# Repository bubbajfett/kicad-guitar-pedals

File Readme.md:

# Current guitar pedal projects 

Current count of pedals in this repo is:  36(?).    Not doing too many more, though I have a FV-1 and a Daisy seed one I'm working on longer term, as well as clearing out the box of shame.

The requirements here are KICAD 7 or later.     Each subdir has a gerbers directory, which has the final set of gerbers used.    

The latest change is to add a PDF in the root of each pedal directory, which has the readme, the schematic as an image, and the front and back layout of the PCB (F.Cu+F.Silkscreen, B.Cu+F.Silkscreen). Also a BOM of the parts is included.    This was all done scripted using kicad-cli  in a VM (Fedora 44, Kicad 10 !!!) as the Kicad 7 versions of this did not work very well.   I will add pics of the real tested boards as an addendum to these.    This change was a result of some feedback I recieved about the lack of clarity of what is in this repo.

These pedals have been a learning exercise for me in KiCad. Any guitar pedal PCB published here has been built and tested. In some cases, more than two versions of boards have been created.   The worst case was 5 versions.

The main idea for doing my own PCB is to allow me to change the footprints and merge and/or hack pedal schematics to come up with new ideas.
The other reason is I am redoing my pedalboard to convert from side-jacks/veroboard layout to  top-jacks/pcbs.   I have gotten to dislike veroboard layouts.

I am an amateur in this.   Also this has been a huge learning exercise.    I've tried to be consistent with some design decisions.

*   back of board mounted POTs.   Tried using both 16mm and 9mm pots (RK97?)
*   common format pinheader so to be able to use 4pin dupont connector or JST connector when building.   The topjacks pcb broke this "common format (9v, Out, In, Gnd --- from left to right)",
in that it was initially intended that the PCB be oriented closest to the the 125B shell bottom, but that made assembly more difficult.   I ordered panels of it from JLPCB, and so I;m just wiring them
backwards.
*   power on the top jack connector, with diode protection there.
*   led on the stomp switch
*   125B form factor.    Top jacks in a 1590B is really hard unless the power connector is modified or moved somewhere else.

One thing I have learned is that the text size on some of these boards is below
the JLPCB minimum recommended size; the text looks fine in osh-park boards.

Several of the build docs have pictures of the final builds.    Tonemachine is the latest...

Putting these pedal layouts out there for any interested party.   Do what you want with them. 

Here are the current repo contents.   These have all been tested outside the box,
and multiple have been successfully boxed.  12  have been boxed and are 
now on the pedalboard. 

| PEDAL | BUILD DOC | Verified|
| ----  | -------   | ------- |
| Delay/deep_blue_delay | [deep-blue-delay](./Delay/deep_blue_delay/deep_blue_delay.pdf) | Y |
| Util/stomp-chargepump |  [stomp-chargepump](./Util/stomp-chargepump/stomp-chargepump.pdf) | Y |
| Util/stomp-3pdt | [stomp-3pdt](./Util/stomp-3pdt/stomp-3pdt.pdf) | Y | 
| Util/top-jacks | [top-jacks](./Util/top-jacks/top-jacks.pdf) | Y |
| Distortion/percolator | [percolator](./Distortion/percolator/percolator.pdf) | Y |
| Distortion/acapulcogold | [acapulcogold](./Distortion/acapulcogold/acapulcogold.pdf) | Y |
| Distortion/fuzzface | [fuzzface](./Distortion/fuzzface/fuzzface.pdf) | Y | 
| Distortion/redllama | [redllama](./Distortion/redllama/redllama.pdf) | Y |
| Distortion/whitefuzz | [whitefuzz](./Distortion/whitefuzz/whitefuzz.pdf) | Y |
| Distortion/bigmuff | [bigmuff](./Distortion/bigmuff/bigmuff.pdf) | Y | 
| Distortion/bigmuff/bmp-ramshead  | --- | Y |
| Distortion/lizardq | [lizardq](./Distortion/lizardq/lizardq.pdf) | Y | 
| Distortion/ejfuzzface | [ejfuzzface](./Distortion/ejfuzzface/ejfuzzface.pdf) | Y | 
| Distortion/tonemachine | [tonemachine](./Distortion/tonemachine/tonemachine.pdf) | Y |
| Distortion/bmp2 | --- | Y |
| Distortion/blackdarling | --- | Y |
| Distortion/900fuzz | --- | Y |
| Compressor/bearhug | [bearhug](./Compressor/bearhug/bearhug.pdf) | Y | 
| Compressor/engineers_thumb | [engineers_thumb](./Compressor/engineers_thumb/engineers_thumb.pdf) | Y |
| Compressor/dynacomp | --- | Y |
| Compressor/dynacomp-lm13700  | --- | N |
| Chorus/littleangel | [littleangel](./Chorus/littleangel/littleangel.pdf) | Y |
| Envelope/mutron | [mutron-v](./Envelope/mutron/mutron.pdf) | Y |
| Overdrive/SFTii | [sftii](./Overdrive/SFTii/SFTii.pdf) | Y | 
| Overdrive/triple_wreck | [triple_wreck](./Overdrive/triple_wreck/triple_wreck.pdf) | Y | 
| Overdrive/ecstacy | [ecstacy](./Overdrive/ecstacy/ecstacy.pdf) | Y | 
| Overdrive/badmonkey | [badmonkey](./Overdrive/badmonkey/badmonkey.pdf) | Y |
| Overdrive/bsiab |  [bsiab](./Overdrive/bsiab/bsiab.pdf) | Y |
| Overdrive/fatdrive | [fatdrive](./Overdrive/fatdrive/fatdrive.pdf)| Y |
| Overdrive/tweed57 | [tweed57](./Overdrive/tweed57/tweed57.pdf)|Y|
| Overdrive/timmy  | [timmy](./Overdrive/timmy/timmy.pdf) | Y |
| Overdrive/KoT | [KoT](./Overdrive/KoT/KoT.pdf) | Y | 
| Overdrive/ocd | [ocd](./Overdrive/ocd/ocd.pdf) | Y |
| Overdrive/revv-g4 | [revv-g4](./Overdrive/revv-g4/revv-g4.pdf) | Y |
| Overdrive/drboogie | ... | Y |
| Overdrive/umble | [umble](./Overdrive/umble/umble.pdf) | Y |
| Equalizer/eq | [eq](./Equalizer/eq/eq.pdf) | Y | 

PCB builds in progress are

*   Barbershop (redo)
*   Klon
*   phase45
*   g2
*   beod    (built, passes sound, but *** so much noise).
*   fy2  (shin-ey fy2)
*   bluesdriver
*   brutalist Jr
*   fortinfuzz
*   katzenkonig
*   paisley
*   plexidrive
*   sabbracadabra
*   tubescreamer

And 4 are stuck in the box of shame 
*   zombiechorus (9 months non-working...)
*   causalty4 phaser  (ugggh ... so close)
*   box of metal      
*   kraken

All the above subprojects have a gerbers/ subdir with the last gerber file I generated. Using OshPark for pcb generation.    They were done with Kicad 7.
Most were done with manual placement of the elements on the PCB, and then using freerouting to autoroute the traces.

License is the general Creative Commons.     Have fun!

All registered trademarks are owned by their respective owners.

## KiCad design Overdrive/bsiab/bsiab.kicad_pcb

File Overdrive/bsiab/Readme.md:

# bsiab

Brown sound in a box.   

Tagboardeffects site introduces it as:

> Brown Sound In A Box version
> 2 (BSIAB2) is an excellent distortion pedal designed by Ed
> Guidry. Based on the AMZ MiniBooster cascading work done by Jack Orman
> and further refined by Aron Nelson and Doug Hammond.

> This is one of the best heavy Marshall-type distortion boxes that
> we've heard and it also performs very well on low drive setting

The schematic here is based on the General Guitar Gadgets BSIAB2 pedal

Very nice sound.

So this pedal circuit  is verified. And I have boxed this one as well.

All trademarks belong to their respective owners.

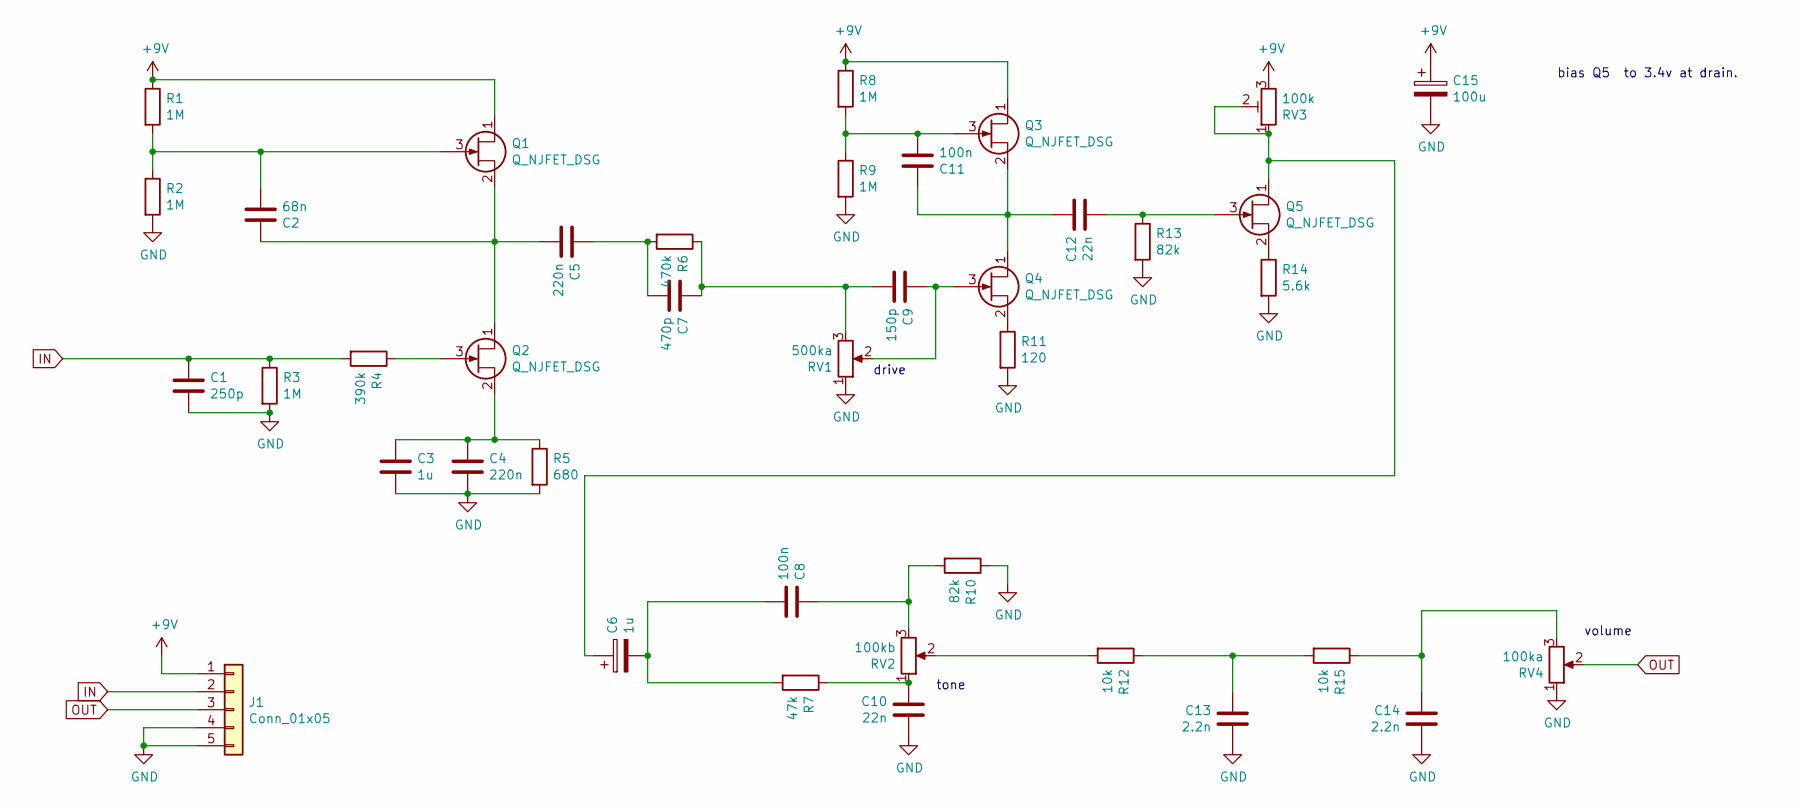
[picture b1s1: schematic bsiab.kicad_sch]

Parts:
C1: 250p; C_Disc_D5.1mm_W3.2mm_P5.00mm
C2: 68n; C_Rect_L7.0mm_W3.5mm_P2.50mm_P5.00mm
C3: 1u; C_Rect_L7.0mm_W3.5mm_P2.50mm_P5.00mm
C4, C5: 220n; C_Rect_L7.0mm_W3.5mm_P2.50mm_P5.00mm
C6: 1u; CP_Radial_D6.3mm_P2.50mm
C7: 470p; C_Disc_D5.1mm_W3.2mm_P5.00mm
C8, C11: 100n; C_Rect_L7.0mm_W3.5mm_P2.50mm_P5.00mm
C9: 150p; C_Disc_D5.1mm_W3.2mm_P5.00mm
C10, C12: 22n; C_Rect_L7.0mm_W3.5mm_P2.50mm_P5.00mm
C13, C14: 2.2n; C_Rect_L7.0mm_W3.5mm_P2.50mm_P5.00mm
C15: 100u; CP_Radial_D6.3mm_P2.50mm
J1: Conn_01x05; PinHeader_1x05_P2.54mm_Vertical
Q1, Q2, Q3, Q4, Q5: Q_NJFET_DSG; TO-92
R1, R2, R3, R8, R9: 1M; R_Axial_DIN0207_L6.3mm_D2.5mm_P10.16mm_Horizontal
R4: 390k; R_Axial_DIN0207_L6.3mm_D2.5mm_P10.16mm_Horizontal
R5: 680; R_Axial_DIN0207_L6.3mm_D2.5mm_P10.16mm_Horizontal
R6: 470k; R_Axial_DIN0207_L6.3mm_D2.5mm_P10.16mm_Horizontal
R7: 47k; R_Axial_DIN0207_L6.3mm_D2.5mm_P10.16mm_Horizontal
R10, R13: 82k; R_Axial_DIN0207_L6.3mm_D2.5mm_P10.16mm_Horizontal
R11: 120; R_Axial_DIN0207_L6.3mm_D2.5mm_P10.16mm_Horizontal
R12, R15: 10k; R_Axial_DIN0207_L6.3mm_D2.5mm_P10.16mm_Horizontal
R14: 5.6k; R_Axial_DIN0207_L6.3mm_D2.5mm_P10.16mm_Horizontal
RV1: 500ka; Potentiometer_Omeg_PC16BU_Vertical
RV2: 100kb; Potentiometer_Omeg_PC16BU_Vertical
RV3: 100k; Potentiometer_Runtron_RM-065_Vertical
RV4: 100ka; Potentiometer_Omeg_PC16BU_Vertical

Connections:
+9V: C15.1, J1.1, Q1.1 (D), Q3.1 (D), R1.1, R8.1, RV3.3
GND: C1.2, C3.2, C4.2, C10.2, C13.2, C14.2, C15.2, J1.4, J1.5, R2.2, R3.2, R5.2, R9.2, R10.1, R11.2, R13.2, R14.2, RV1.1, RV4.1
IN: C1.1, J1.2, R3.1, R4.2
unnamed: C2.1, C5.2, Q1.2 (S), Q2.1 (D)
unnamed: C2.2, Q1.3 (G), R1.2, R2.1
unnamed: C3.1, C4.1, Q2.2 (S), R5.1
unnamed: C5.1, C7.2, R6.2
unnamed: C6.1, Q5.1 (D), RV3.1, RV3.2
unnamed: C6.2, C8.2, R7.2
unnamed: C7.1, C9.2, R6.1, RV1.3
unnamed: C8.1, R10.2, RV2.3
unnamed: C9.1, Q4.3 (G), RV1.2
unnamed: C10.1, R7.1, RV2.1
unnamed: C11.1, C12.1, Q3.2 (S), Q4.1 (D)
unnamed: C11.2, Q3.3 (G), R8.2, R9.1
unnamed: C12.2, Q5.3 (G), R13.1
unnamed: C13.1, R12.1, R15.2
unnamed: C14.1, R15.1, RV4.3
unnamed: Q2.3 (G), R4.1
unnamed: Q4.2 (S), R11.1
unnamed: Q5.2 (S), R14.1
unnamed: R12.2, RV2.2
OUT: J1.3, RV4.2

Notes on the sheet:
bias Q5 to 3.4v at drain.
volume
drive
tone

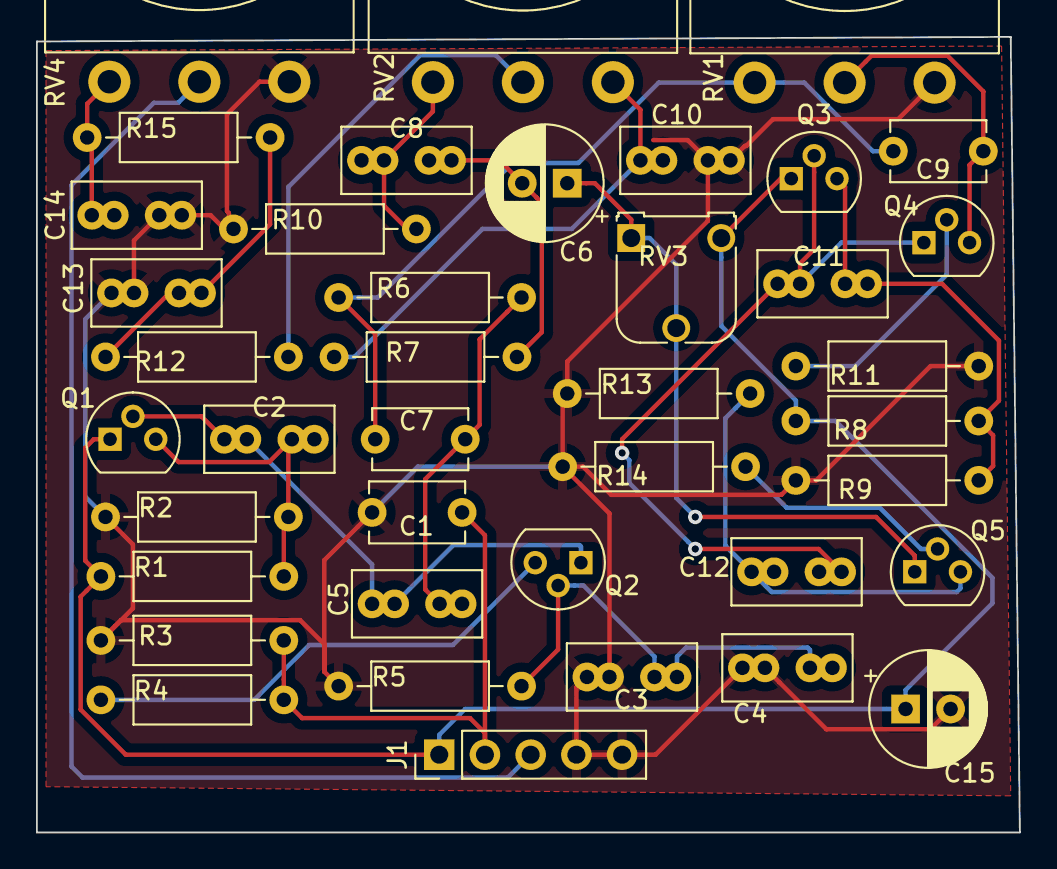
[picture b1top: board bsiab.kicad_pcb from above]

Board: 2 copper layers, 54.6 x 44.2 mm, 40 parts (0 on the bottom side), 23 nets.

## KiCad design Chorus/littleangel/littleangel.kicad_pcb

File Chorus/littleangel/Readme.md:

# Little Angel 

This is a clone Rick Holt's  Little Angel Chorus.

This was based on the a schematic I found on the web for this.
THis has the "Vibe Switch Mod" someone did,  which changes
between vibrato and chorus modes.    Nice pedal.

All trademarks belong to their respective owners.

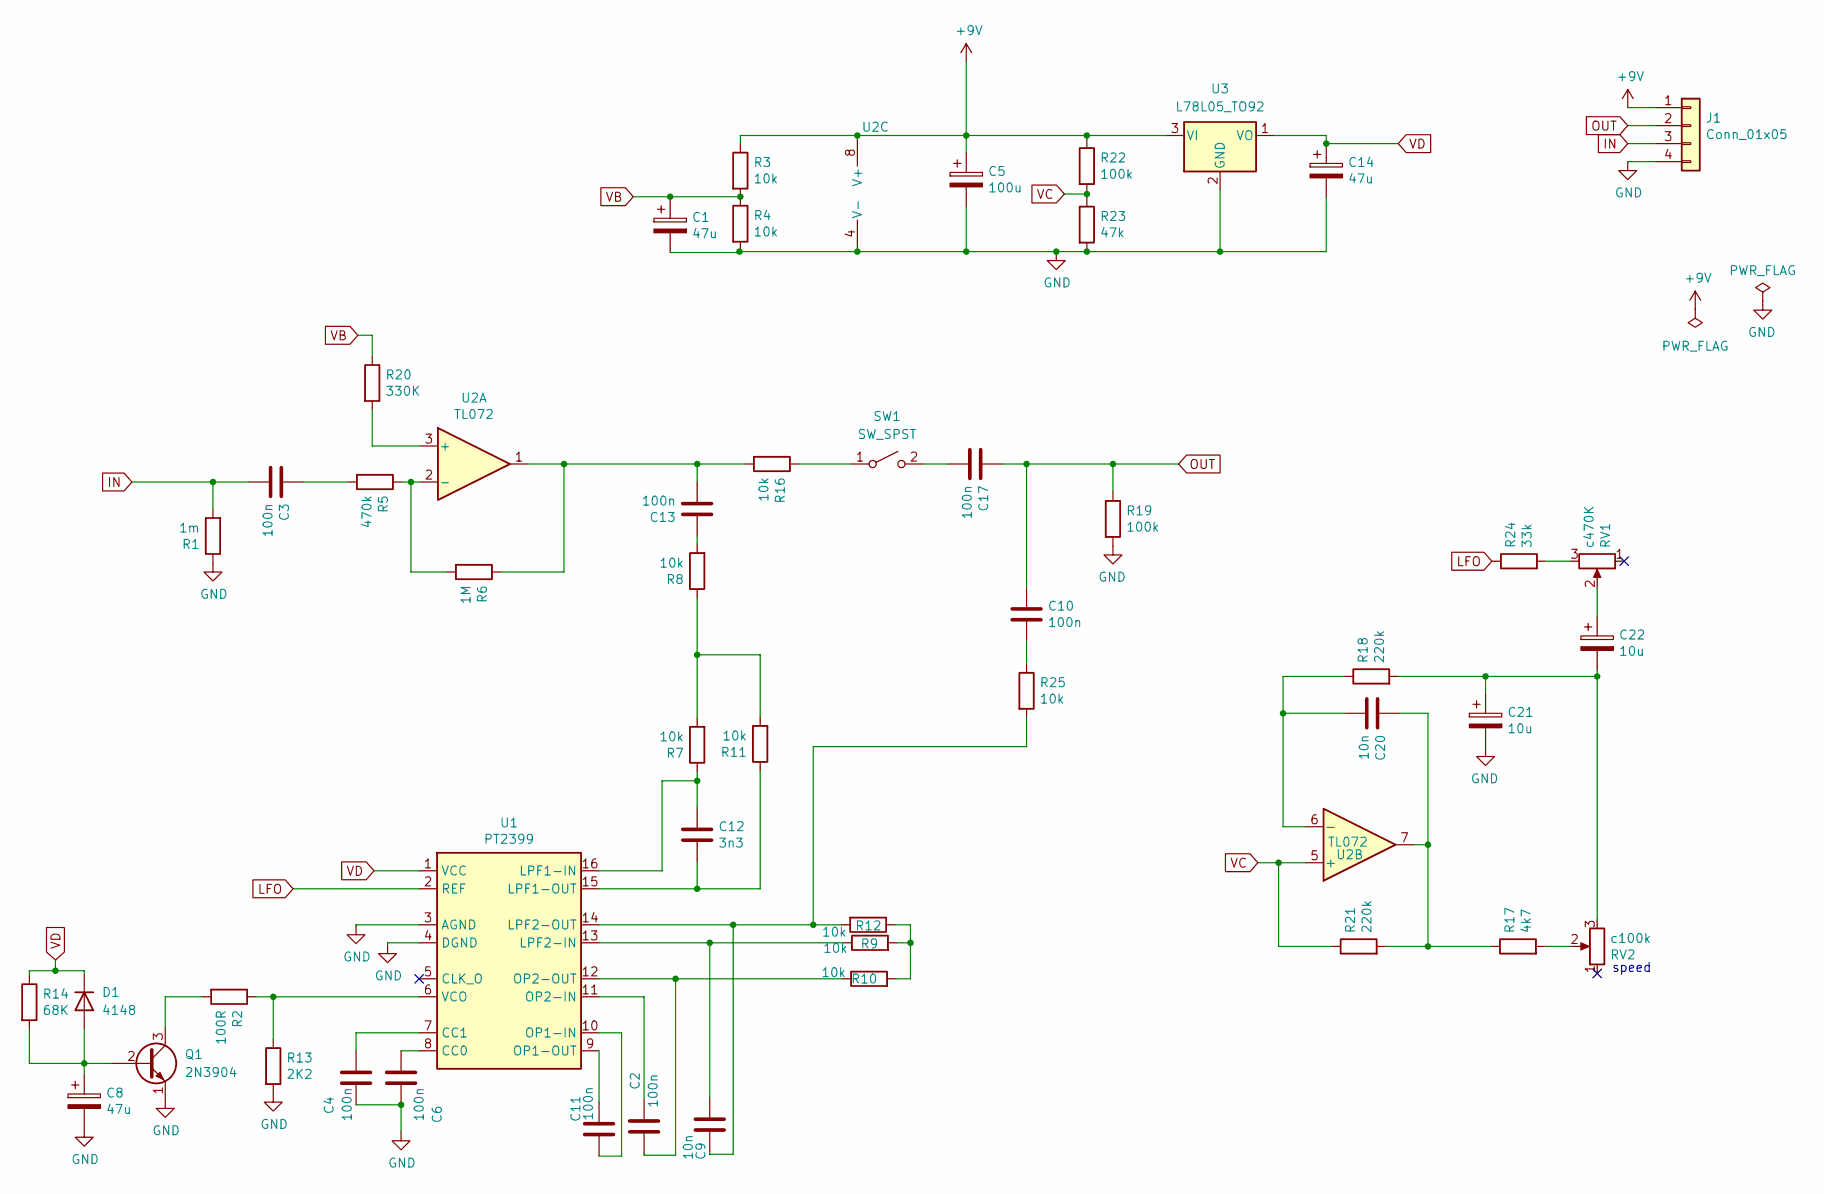
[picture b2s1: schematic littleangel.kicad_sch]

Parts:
C1, C8, C14: 47u; CP_Radial_D5.0mm_P2.00mm
C2, C3, C4, C6, C10, C11, C13, C17: 100n; C_Rect_L7.0mm_W3.5mm_P5.00mm
C5: 100u; CP_Radial_D6.3mm_P2.50mm
C9, C20: 10n; C_Rect_L7.0mm_W3.5mm_P5.00mm
C12: 3n3; C_Rect_L7.0mm_W3.5mm_P5.00mm
C21, C22: 10u; CP_Radial_D5.0mm_P2.00mm
D1: 4148; D_A-405_P7.62mm_Horizontal
J1: Conn_01x05; PinHeader_1x04_P2.54mm_Vertical
Q1: 2N3904; TO-92_Inline
R1: 1m; R_Axial_DIN0207_L6.3mm_D2.5mm_P10.16mm_Horizontal
R2: 100R; R_Axial_DIN0207_L6.3mm_D2.5mm_P10.16mm_Horizontal
R3, R4, R7, R8, R9, R10, R11, R12, R16, R25: 10k; R_Axial_DIN0207_L6.3mm_D2.5mm_P10.16mm_Horizontal
R5: 470k; R_Axial_DIN0207_L6.3mm_D2.5mm_P10.16mm_Horizontal
R6: 1M; R_Axial_DIN0207_L6.3mm_D2.5mm_P10.16mm_Horizontal
R13: 2K2; R_Axial_DIN0207_L6.3mm_D2.5mm_P10.16mm_Horizontal
R14: 68K; R_Axial_DIN0207_L6.3mm_D2.5mm_P10.16mm_Horizontal
R17: 4k7; R_Axial_DIN0207_L6.3mm_D2.5mm_P10.16mm_Horizontal
R18, R21: 220k; R_Axial_DIN0207_L6.3mm_D2.5mm_P10.16mm_Horizontal
R19, R22: 100k; R_Axial_DIN0207_L6.3mm_D2.5mm_P10.16mm_Horizontal
R20: 330K; R_Axial_DIN0207_L6.3mm_D2.5mm_P10.16mm_Horizontal
R23: 47k; R_Axial_DIN0207_L6.3mm_D2.5mm_P10.16mm_Horizontal
R24: 33k; R_Axial_DIN0207_L6.3mm_D2.5mm_P10.16mm_Horizontal
RV1: c470K; Pot_Underside
RV2: c100k; Pot_Underside
SW1: SW_SPST; SWITCH-M1-SPDT
U1: PT2399; DIP-16_W7.62mm
U2: TL072; DIP-8_W7.62mm
U3: L78L05_TO92; TO-92_Inline

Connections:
+9V: C5.1, J1.1, R3.1, R22.1, U2.8 (V+), U3.3 (VI)
GND: C1.2, C4.1, C5.2, C6.1, C8.2, C14.2, C21.2, J1.4, Q1.1 (E), R1.1, R4.2, R13.2, R19.2, R23.2, U1.3 (AGND), U1.4 (DGND), U2.4 (V-), U3.2 (GND)
IN: C3.2, J1.3, R1.2
LFO: R24.1, U1.2 (REF)
unnamed: C3.1, R5.2
unnamed: C10.2, R25.1
unnamed: C13.1, R8.2
unnamed: C13.2, R6.1, R16.2, U2.1
unnamed: C20.1, R17.1, R21.2, U2.7
unnamed: C21.1, C22.2, R18.2, RV2.3
unnamed: C22.1, RV1.2
unnamed: C8.1, D1.2 (A), Q1.2 (B), R14.2
unnamed: Q1.3 (C), R2.2
unnamed: R9.2, R10.2, R12.1
unnamed: R7.2, R8.1, R11.2
unnamed: R17.2, RV2.2
unnamed: R24.2, RV1.3
unnamed: R16.1, SW1.1 (A)
unnamed: C17.2, SW1.2 (B)
unnamed: C6.2, U1.8 (CC0)
unnamed: C4.2, U1.7 (CC1)
unnamed: C12.1, R7.1, U1.16 (LPF1-IN)
unnamed: C12.2, R11.1, U1.15 (LPF1-OUT)
unnamed: C9.1, R9.1, U1.13 (LPF2-IN)
unnamed: C9.2, R12.2, R25.2, U1.14 (LPF2-OUT)
unnamed: C11.1, U1.10 (OP1-IN)
unnamed: C11.2, U1.9 (OP1-OUT)
unnamed: C2.1, U1.11 (OP2-IN)
unnamed: C2.2, R10.1, U1.12 (OP2-OUT)
unnamed: R2.1, R13.1, U1.6 (VCO)
unnamed: R20.2, U2.3 (+)
unnamed: R5.1, R6.2, U2.2 (-)
unnamed: C20.2, R18.1, U2.6 (-)
OUT: C10.1, C17.1, J1.2, R19.1
VB: C1.1, R3.2, R4.1, R20.1
VC: R21.1, R22.2, R23.1, U2.5 (+)
VD: C14.1, D1.1 (K), R14.1, U1.1 (VCC), U3.1 (VO)

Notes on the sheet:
speed

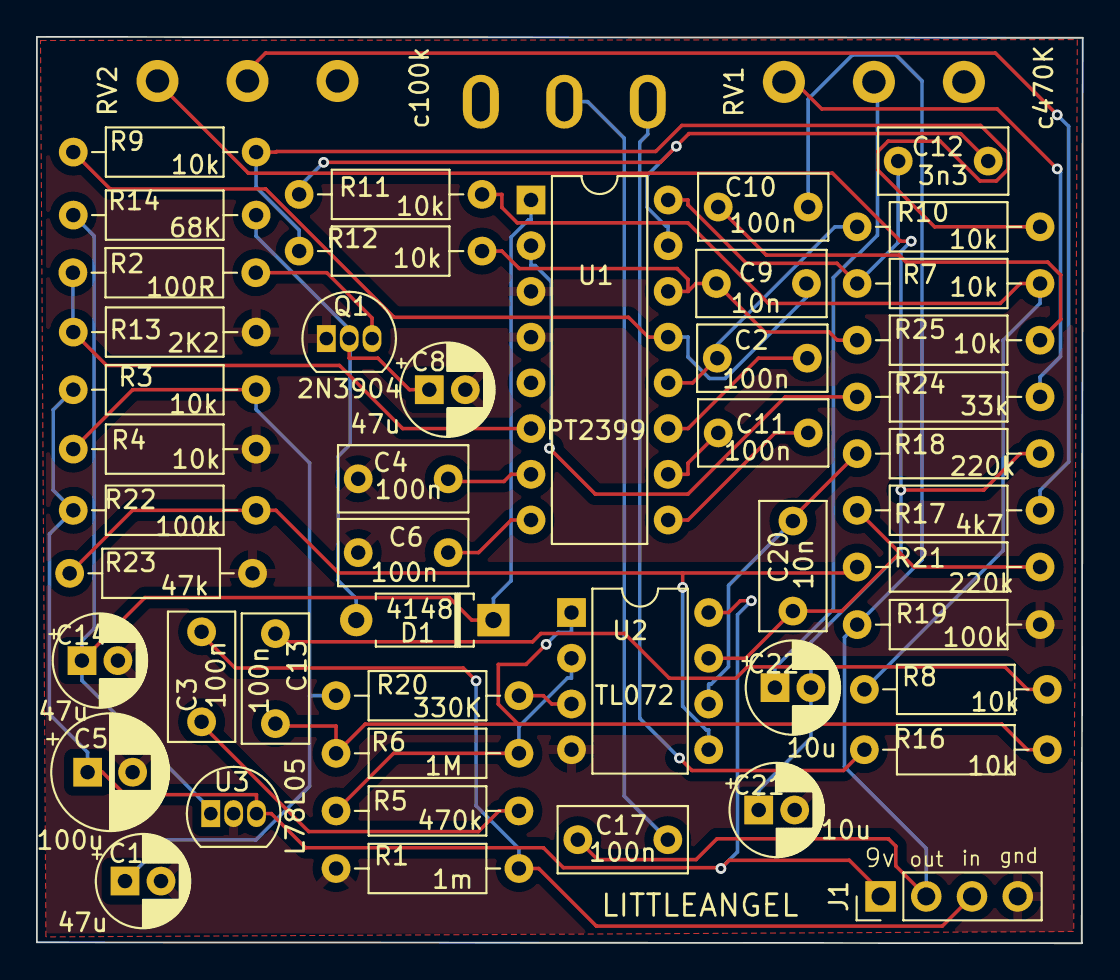
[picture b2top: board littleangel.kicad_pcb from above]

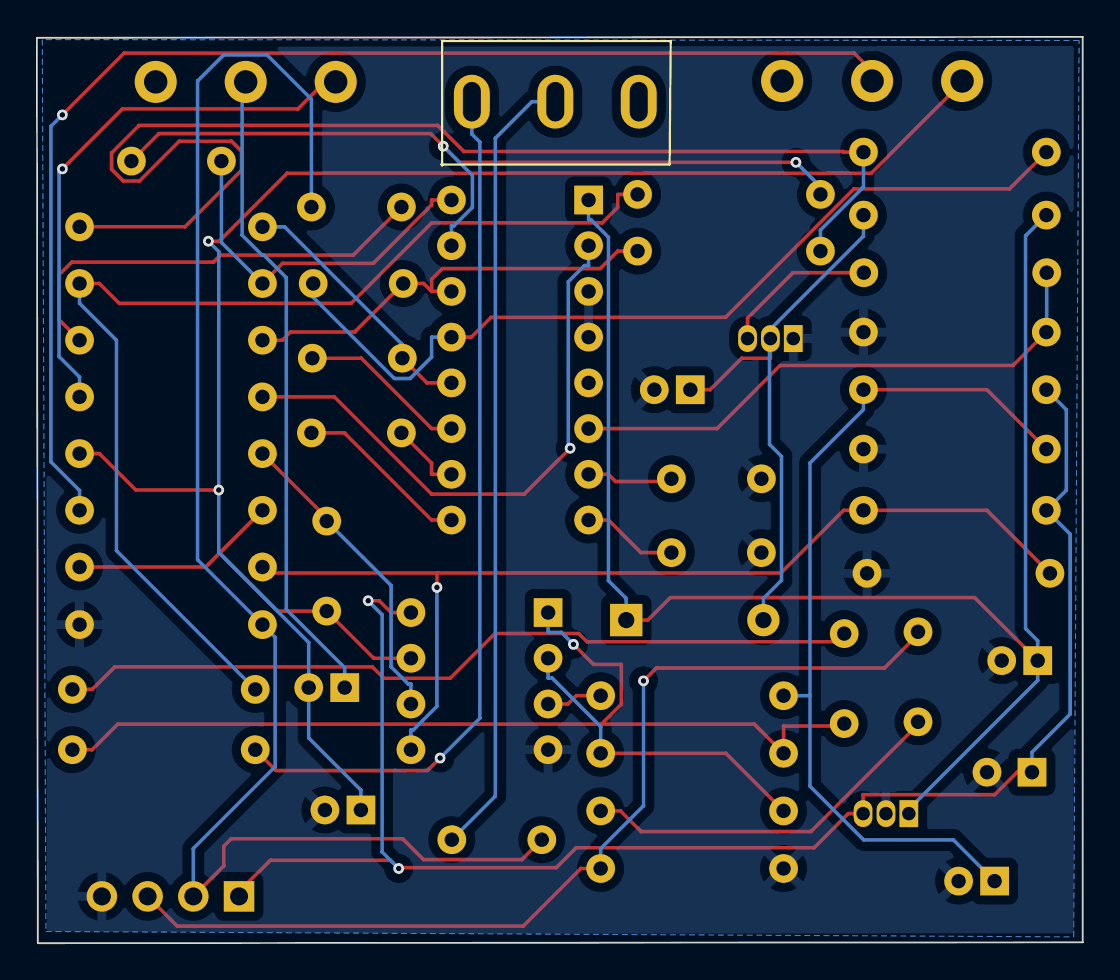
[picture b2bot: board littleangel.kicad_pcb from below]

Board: 2 copper layers, 58.1 x 50.3 mm, 50 parts (3 on the bottom side), 37 nets.

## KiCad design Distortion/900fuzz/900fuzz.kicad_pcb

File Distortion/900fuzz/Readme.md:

# 900 Fuzz

This is a clone of the 900 Fuzz by Fairfield Circuitry.

The first build had a "non-connected" base of Q4. I missed it, and
none of the kicad rules-checker caught it, or I ignored it.   Anyway,
the 2nd try I was more careful not to ignore any ERC errors.

This was based on the Pedalpcb NeinFuzz schematic, which does not specify the JFET.    Dirtboxlayouts shows J201

All trademarks belong to their respective owners.

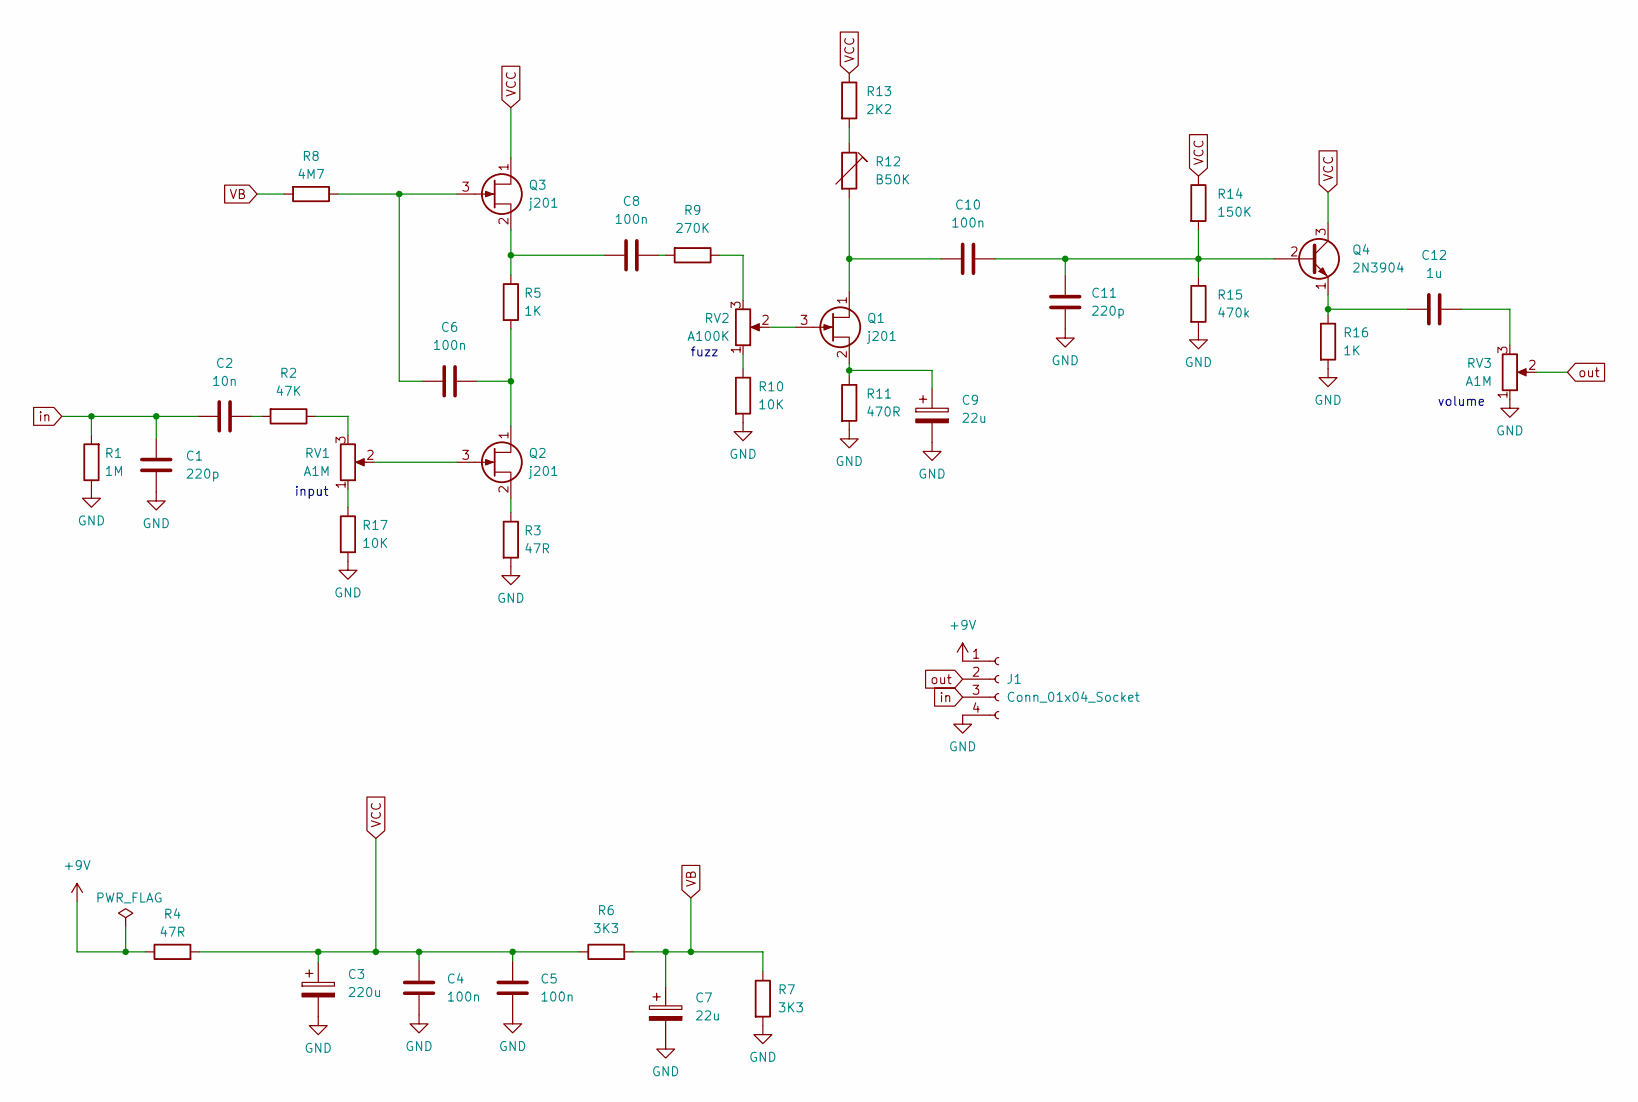
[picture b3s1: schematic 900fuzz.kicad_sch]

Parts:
C1, C11: 220p; C_Disc_D5.0mm_W2.5mm_P2.50mm
C2: 10n; C_Rect_L7.0mm_W2.5mm_P5.00mm
C3: 220u; CP_Radial_D6.3mm_P2.50mm
C4, C5, C6, C8, C10: 100n; C_Rect_L7.0mm_W2.5mm_P5.00mm
C7, C9: 22u; CP_Radial_D5.0mm_P2.00mm
C12: 1u; C_Rect_L7.0mm_W2.5mm_P5.00mm
J1: Conn_01x04_Socket; PinHeader_1x04_P2.54mm_Vertical
Q1, Q2, Q3: j201; TO92-SMD
Q4: 2N3904; TO-92_Inline_Wide
R1: 1M; R_Axial_DIN0207_L6.3mm_D2.5mm_P10.16mm_Horizontal
R2: 47K; R_Axial_DIN0207_L6.3mm_D2.5mm_P10.16mm_Horizontal
R3, R4: 47R; R_Axial_DIN0207_L6.3mm_D2.5mm_P10.16mm_Horizontal
R5, R16: 1K; R_Axial_DIN0207_L6.3mm_D2.5mm_P10.16mm_Horizontal
R6, R7: 3K3; R_Axial_DIN0207_L6.3mm_D2.5mm_P10.16mm_Horizontal
R8: 4M7; R_Axial_DIN0207_L6.3mm_D2.5mm_P10.16mm_Horizontal
R9: 270K; R_Axial_DIN0207_L6.3mm_D2.5mm_P10.16mm_Horizontal
R10, R17: 10K; R_Axial_DIN0207_L6.3mm_D2.5mm_P10.16mm_Horizontal
R11: 470R; R_Axial_DIN0207_L6.3mm_D2.5mm_P10.16mm_Horizontal
R12: B50K; Potentiometer_Runtron_RM-065_Vertical
R13: 2K2; R_Axial_DIN0207_L6.3mm_D2.5mm_P10.16mm_Horizontal
R14: 150K; R_Axial_DIN0207_L6.3mm_D2.5mm_P10.16mm_Horizontal
R15: 470k; R_Axial_DIN0207_L6.3mm_D2.5mm_P10.16mm_Horizontal
RV1, RV3: A1M; Pot_Underside
RV2: A100K; Pot_Underside

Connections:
+9V: J1.1, R4.1
GND: C1.2, C3.2, C4.1, C5.1, C7.2, C9.2, C11.1, J1.4, R1.1, R3.2, R7.2, R10.2, R11.2, R15.2, R16.2, R17.2, RV3.1
unnamed: C2.2, R2.2
unnamed: C8.2, R9.2
unnamed: C12.2, RV3.3
unnamed: C10.1, Q1.1 (D), R12.2
unnamed: Q1.3 (G), RV2.2
unnamed: C9.1, Q1.2 (S), R11.1
unnamed: C6.2, Q2.1 (D), R5.2
unnamed: Q2.3 (G), RV1.2
unnamed: Q2.2 (S), R3.1
unnamed: C6.1, Q3.3 (G), R8.1
unnamed: C8.1, Q3.2 (S), R5.1
unnamed: C10.2, C11.2, Q4.2 (B), R14.2, R15.1
unnamed: C12.1, Q4.1 (E), R16.1
unnamed: R2.1, RV1.3
unnamed: R9.1, RV2.3
unnamed: R10.1, RV2.1
unnamed: R12.1, R13.2
unnamed: R17.1, RV1.1
VB: C7.1, R6.2, R7.1, R8.2
VCC: C3.1, C4.2, C5.2, Q3.1 (D), Q4.3 (C), R4.2, R6.1, R13.1, R14.1
in: C1.1, C2.1, J1.3, R1.2
out: J1.2, RV3.2

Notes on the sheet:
volume
fuzz
input

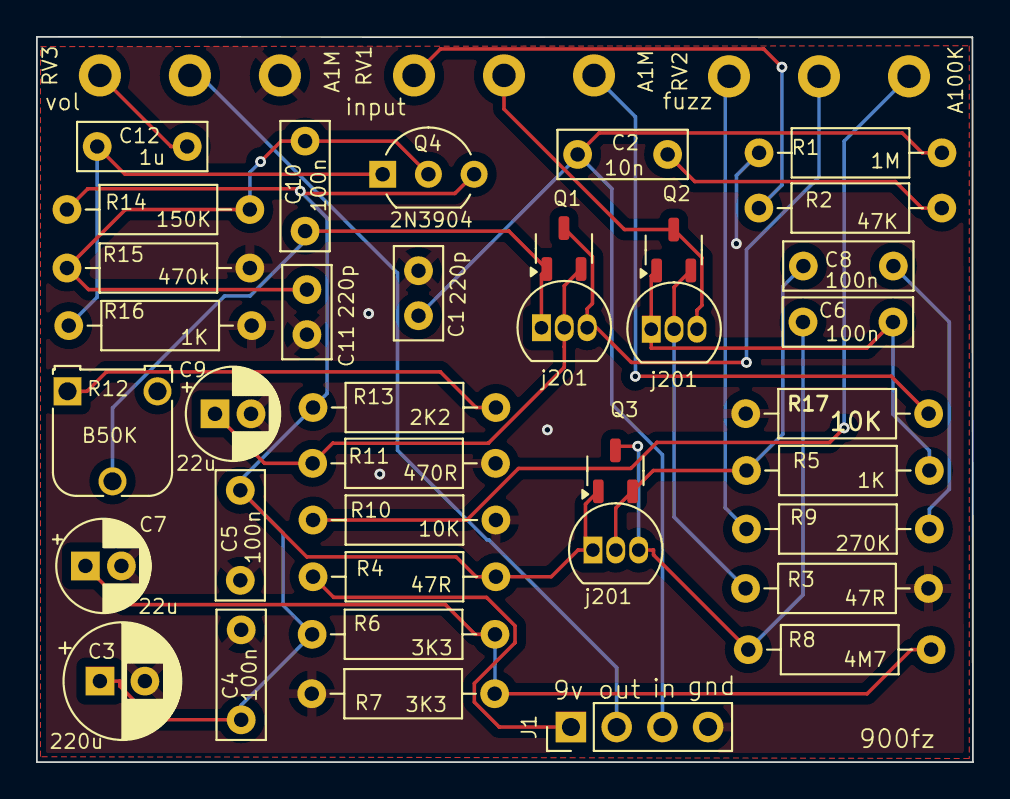
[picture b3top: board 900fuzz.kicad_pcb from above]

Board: 2 copper layers, 52.0 x 40.3 mm, 37 parts (0 on the bottom side), 24 nets.

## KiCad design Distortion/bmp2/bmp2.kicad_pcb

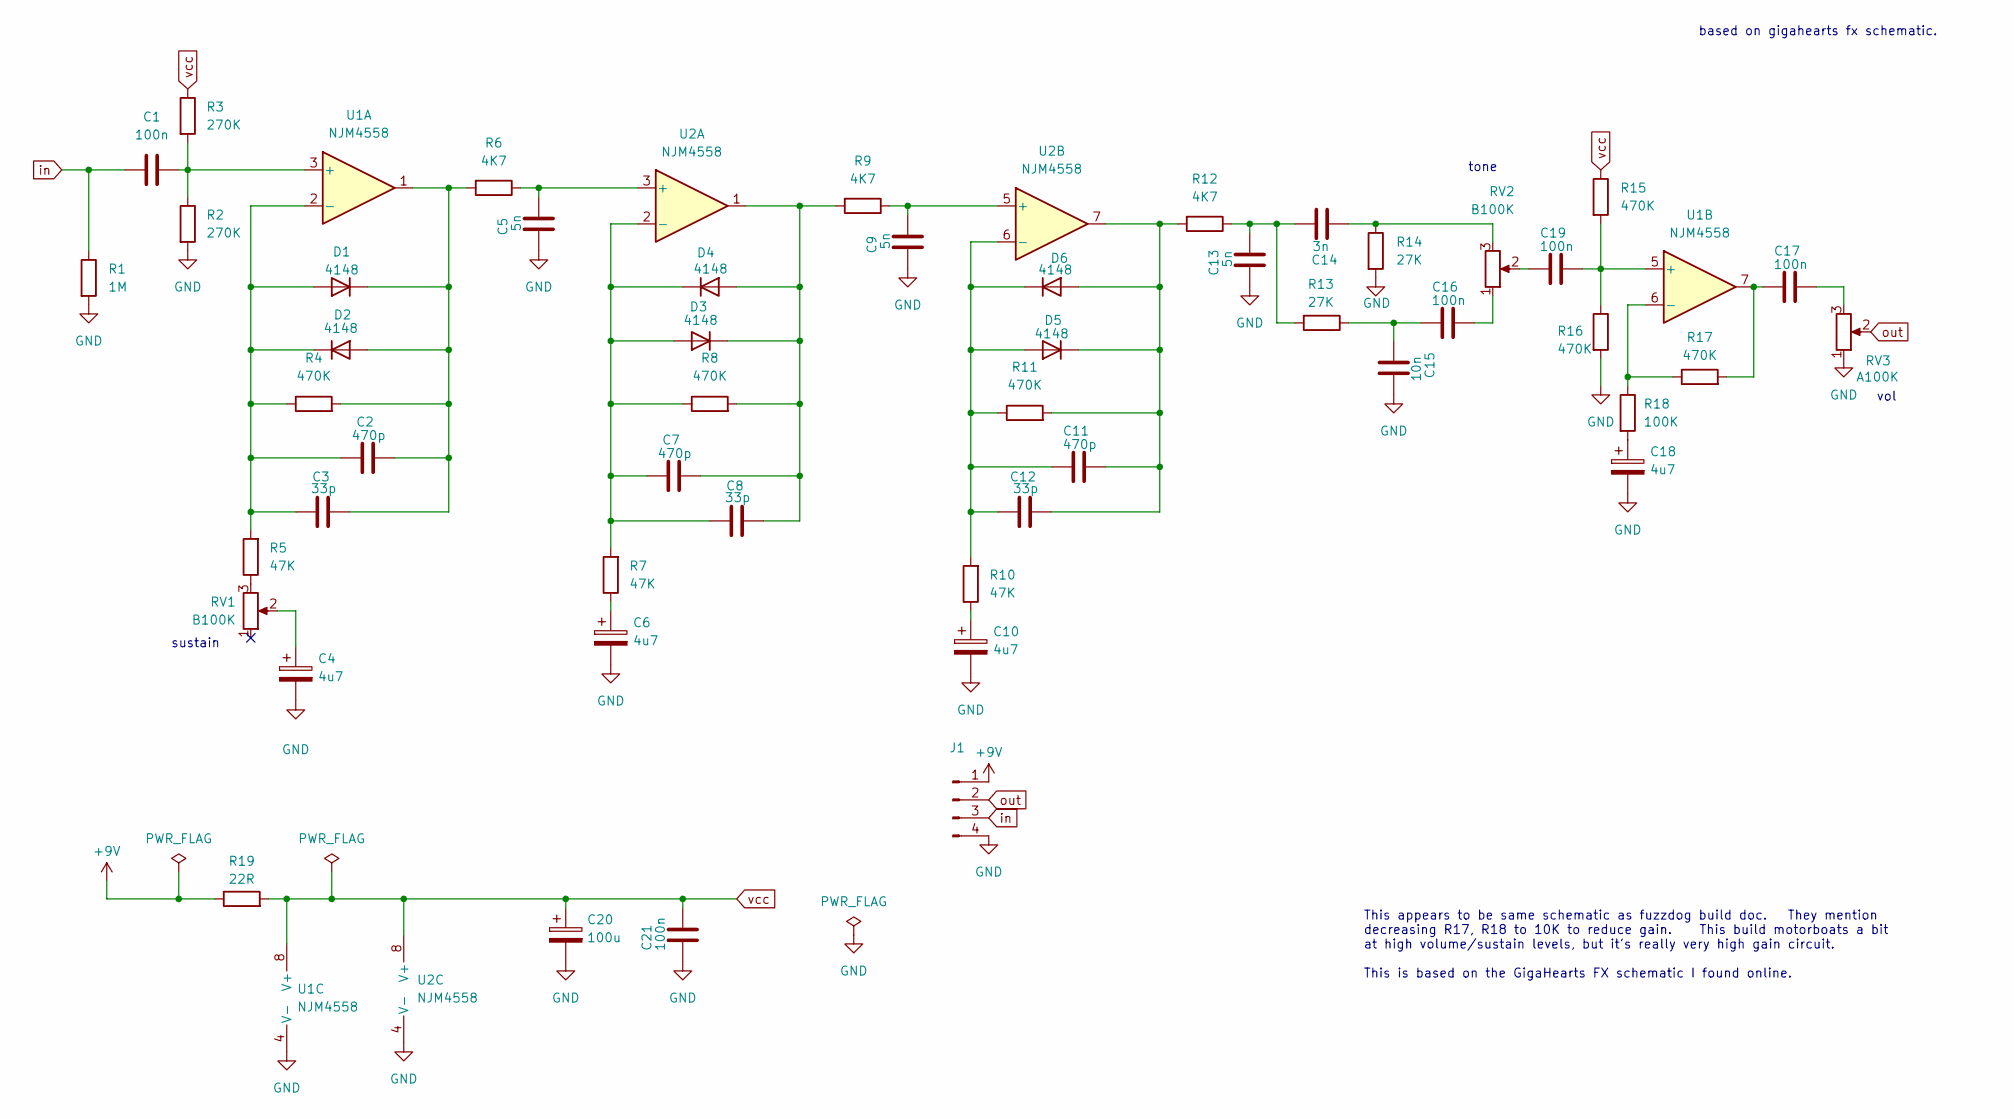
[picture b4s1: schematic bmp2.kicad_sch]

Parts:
C1, C16, C17, C19, C21: 100n; C_Rect_L7.0mm_W2.5mm_P5.00mm
C2, C7, C11: 470p; C_Disc_D5.0mm_W2.5mm_P2.50mm
C3, C8, C12: 33p; C_Disc_D5.0mm_W2.5mm_P2.50mm
C4, C6, C10, C18: 4u7; CP_Radial_D5.0mm_P2.00mm
C5, C9, C13: 5n; C_Rect_L7.0mm_W2.5mm_P5.00mm
C14: 3n; C_Rect_L7.0mm_W2.5mm_P5.00mm
C15: 10n; C_Rect_L7.0mm_W2.5mm_P5.00mm
C20: 100u; CP_Radial_D8.0mm_P2.50mm
D1, D2, D3, D4, D5, D6: 4148; D_DO-35_SOD27_P7.62mm_Horizontal
J1: Conn_01x04_Pin; PinHeader_1x04_P2.54mm_Vertical
R1: 1M; R_Axial_DIN0207_L6.3mm_D2.5mm_P10.16mm_Horizontal
R2, R3: 270K; R_Axial_DIN0207_L6.3mm_D2.5mm_P10.16mm_Horizontal
R4, R8, R11, R15, R16, R17: 470K; R_Axial_DIN0207_L6.3mm_D2.5mm_P10.16mm_Horizontal
R5, R7, R10: 47K; R_Axial_DIN0207_L6.3mm_D2.5mm_P10.16mm_Horizontal
R6, R9, R12: 4K7; R_Axial_DIN0207_L6.3mm_D2.5mm_P10.16mm_Horizontal
R13, R14: 27K; R_Axial_DIN0207_L6.3mm_D2.5mm_P10.16mm_Horizontal
R18: 100K; R_Axial_DIN0207_L6.3mm_D2.5mm_P10.16mm_Horizontal
R19: 22R; R_Axial_DIN0207_L6.3mm_D2.5mm_P10.16mm_Horizontal
RV1, RV2: B100K; Pot_Underside
RV3: A100K; Pot_Underside
U1, U2: NJM4558; DIP-8_W7.62mm

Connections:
+9V: J1.1, R19.1
GND: C4.2, C5.1, C6.2, C9.1, C10.2, C13.1, C15.2, C18.2, C20.2, C21.1, J1.4, R1.2, R2.2, R14.2, R16.2, RV3.1, U1.4 (V-), U2.4 (V-)
unnamed: C4.1, RV1.2
unnamed: C6.1, R7.1
unnamed: C10.1, R10.1
unnamed: C13.2, C14.2, R12.1, R13.2
unnamed: C14.1, R14.1, RV2.3
unnamed: C15.1, C16.1, R13.1
unnamed: C16.2, RV2.1
unnamed: C17.1, R17.2, U1.7
unnamed: C17.2, RV3.3
unnamed: C18.1, R18.2
unnamed: C19.1, RV2.2
unnamed: C2.1, C3.1, D1.2 (A), D2.1 (K), R4.1, R5.2, U1.2 (-)
unnamed: C2.2, C3.2, D1.1 (K), D2.2 (A), R4.2, R6.2, U1.1
unnamed: C7.1, C8.1, D3.2 (A), D4.1 (K), R7.2, R8.1, U2.2 (-)
unnamed: C7.2, C8.2, D3.1 (K), D4.2 (A), R8.2, R9.2, U2.1
unnamed: C11.1, C12.1, D5.2 (A), D6.1 (K), R10.2, R11.1, U2.6 (-)
unnamed: C11.2, C12.2, D5.1 (K), D6.2 (A), R11.2, R12.2, U2.7
unnamed: R5.1, RV1.3
unnamed: C1.2, R2.1, R3.2, U1.3 (+)
unnamed: C19.2, R15.2, R16.1, U1.5 (+)
unnamed: R17.1, R18.1, U1.6 (-)
unnamed: C5.2, R6.1, U2.3 (+)
unnamed: C9.2, R9.1, U2.5 (+)
in: C1.1, J1.3, R1.1
out: J1.2, RV3.2
vcc: C20.1, C21.2, R3.1, R15.1, R19.2, U1.8 (V+), U2.8 (V+)

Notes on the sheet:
vol
tone
sustain
This appears to be same schematic as fuzzdog build doc. They mention decreasing R17, R18 to 10K to reduce gain. This build motorboats a bit at high volume/sustain levels, but it's really very high gain circuit. This is based on the GigaHearts FX schematic I found online.
based on gigahearts fx schematic.

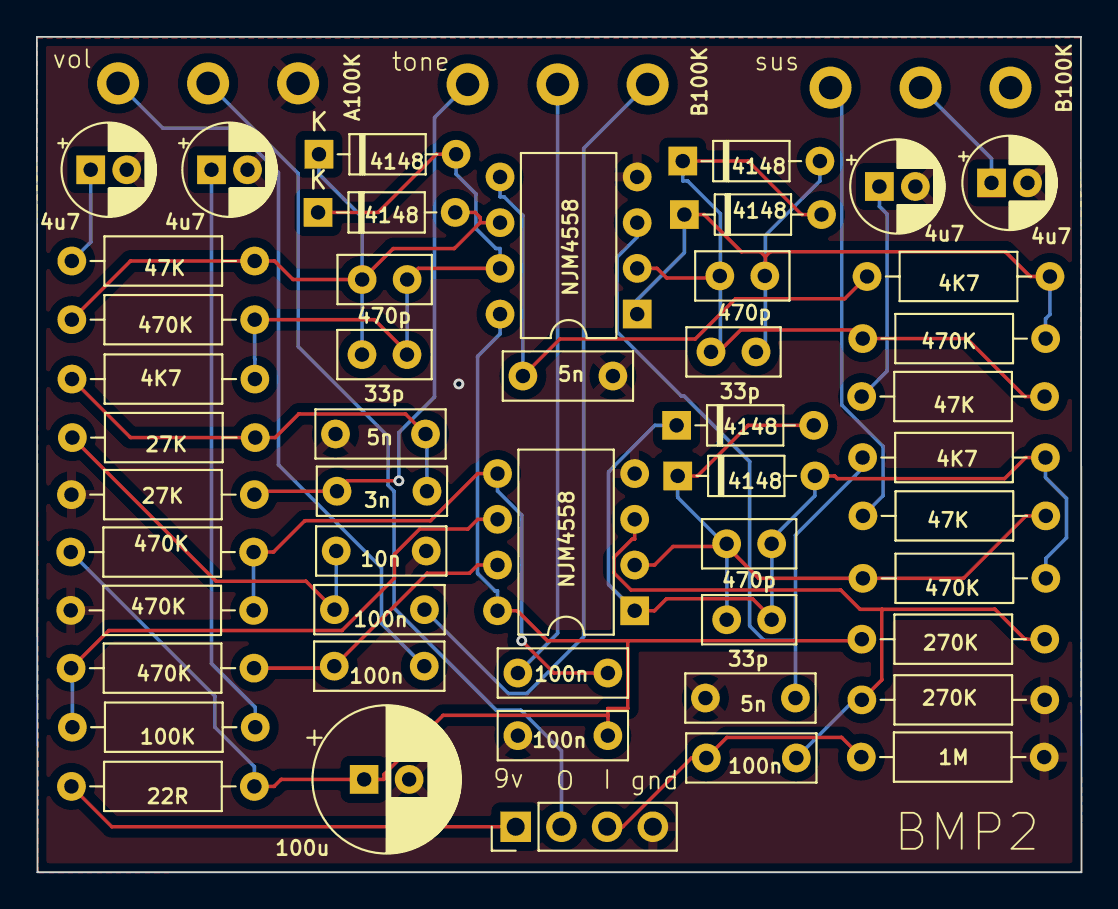
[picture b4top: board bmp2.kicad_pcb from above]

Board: 2 copper layers, 58.0 x 46.4 mm, 52 parts (0 on the bottom side), 28 nets.
